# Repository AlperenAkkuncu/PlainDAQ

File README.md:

# PlainDAQ

PlainDAQ is a module that turns your Raspberry Pi Pico into a simple, precision 4-channel oscilloscope and a single channel function generator. Optionally it can also include a Wi-Fi module to add wireless capability to Raspberry Pi Pico modules.

To put it other words, PlainDAQ is a simple, useful tool to add basic precision analog functionality to your Raspberry Pi Pico board. It has a precision, low-noise, low-drift 12-bit 500kSPS/s ADC, sampling 4-channels and supporting 3 ranges (±1V, ±2V, ±4V). It also has a 10-bit DAC which helps create analog outputs and waveforms and it has a single range of ±4V.

Short List of features:

Analog Inputs:
• 4 Channels (multiplexed)  
• 12-bit resolution, 72dB SNR (11.6 ENOB,4000:1 dynamic range)  
• 500 kS/s sampling rate. 
• ±1V, ±2V, ±4V bipolar ranges.  

Analog Output:  
• 10-bit resolution.  
• 50 kS/s sampling rate.  
• ±4V bipolar range.  

Voltage Reference:
• 2.5V, 20ppm/°C (Typical) Drift  
• Calibrate to 0.05%, Stored in as ROM as calibration data. 

Bipolar Voltage Supply: 
• ±5V power output.   
• ±100mA current rating.    

ESP-WROOM-02D AT-Command Module:
• Simple UART interface to Raspberry Pico
• Wi-Fi connectivity    
• Shipped with ESP AT firmware 

# Here are some nice pictures of PlainDAQ

### Filter! More on that later

### The kit!

## PlainDAQ Connections

## PlainDAQ Components

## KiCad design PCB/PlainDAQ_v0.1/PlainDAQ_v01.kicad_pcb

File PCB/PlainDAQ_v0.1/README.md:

### !!DO NOT USE IT AS A REFERENCE!!
### This is an old version of PlainDAQ

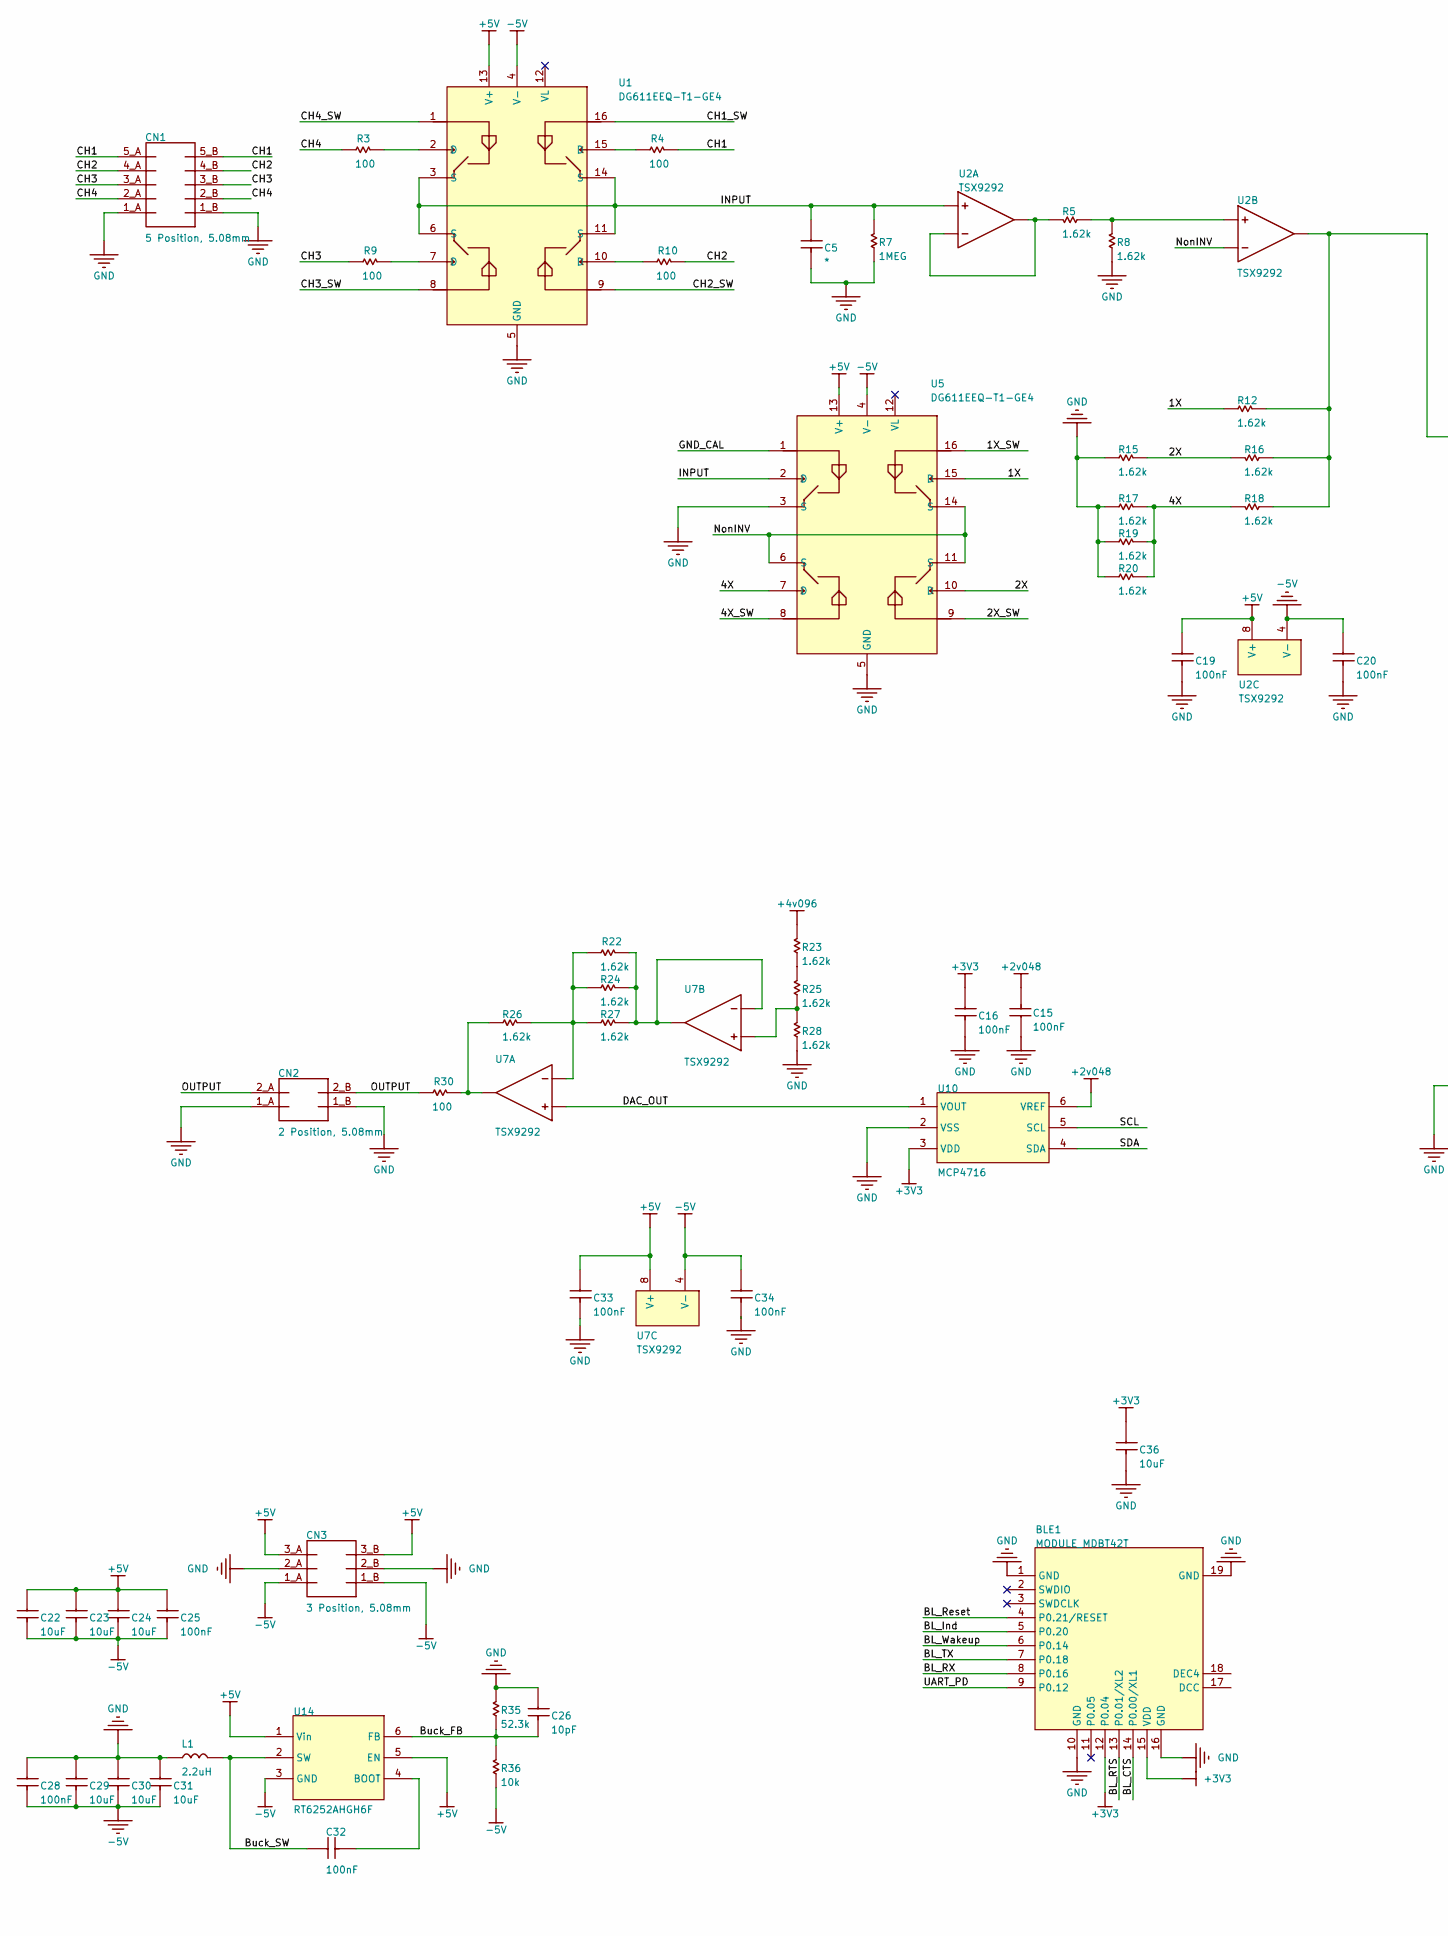
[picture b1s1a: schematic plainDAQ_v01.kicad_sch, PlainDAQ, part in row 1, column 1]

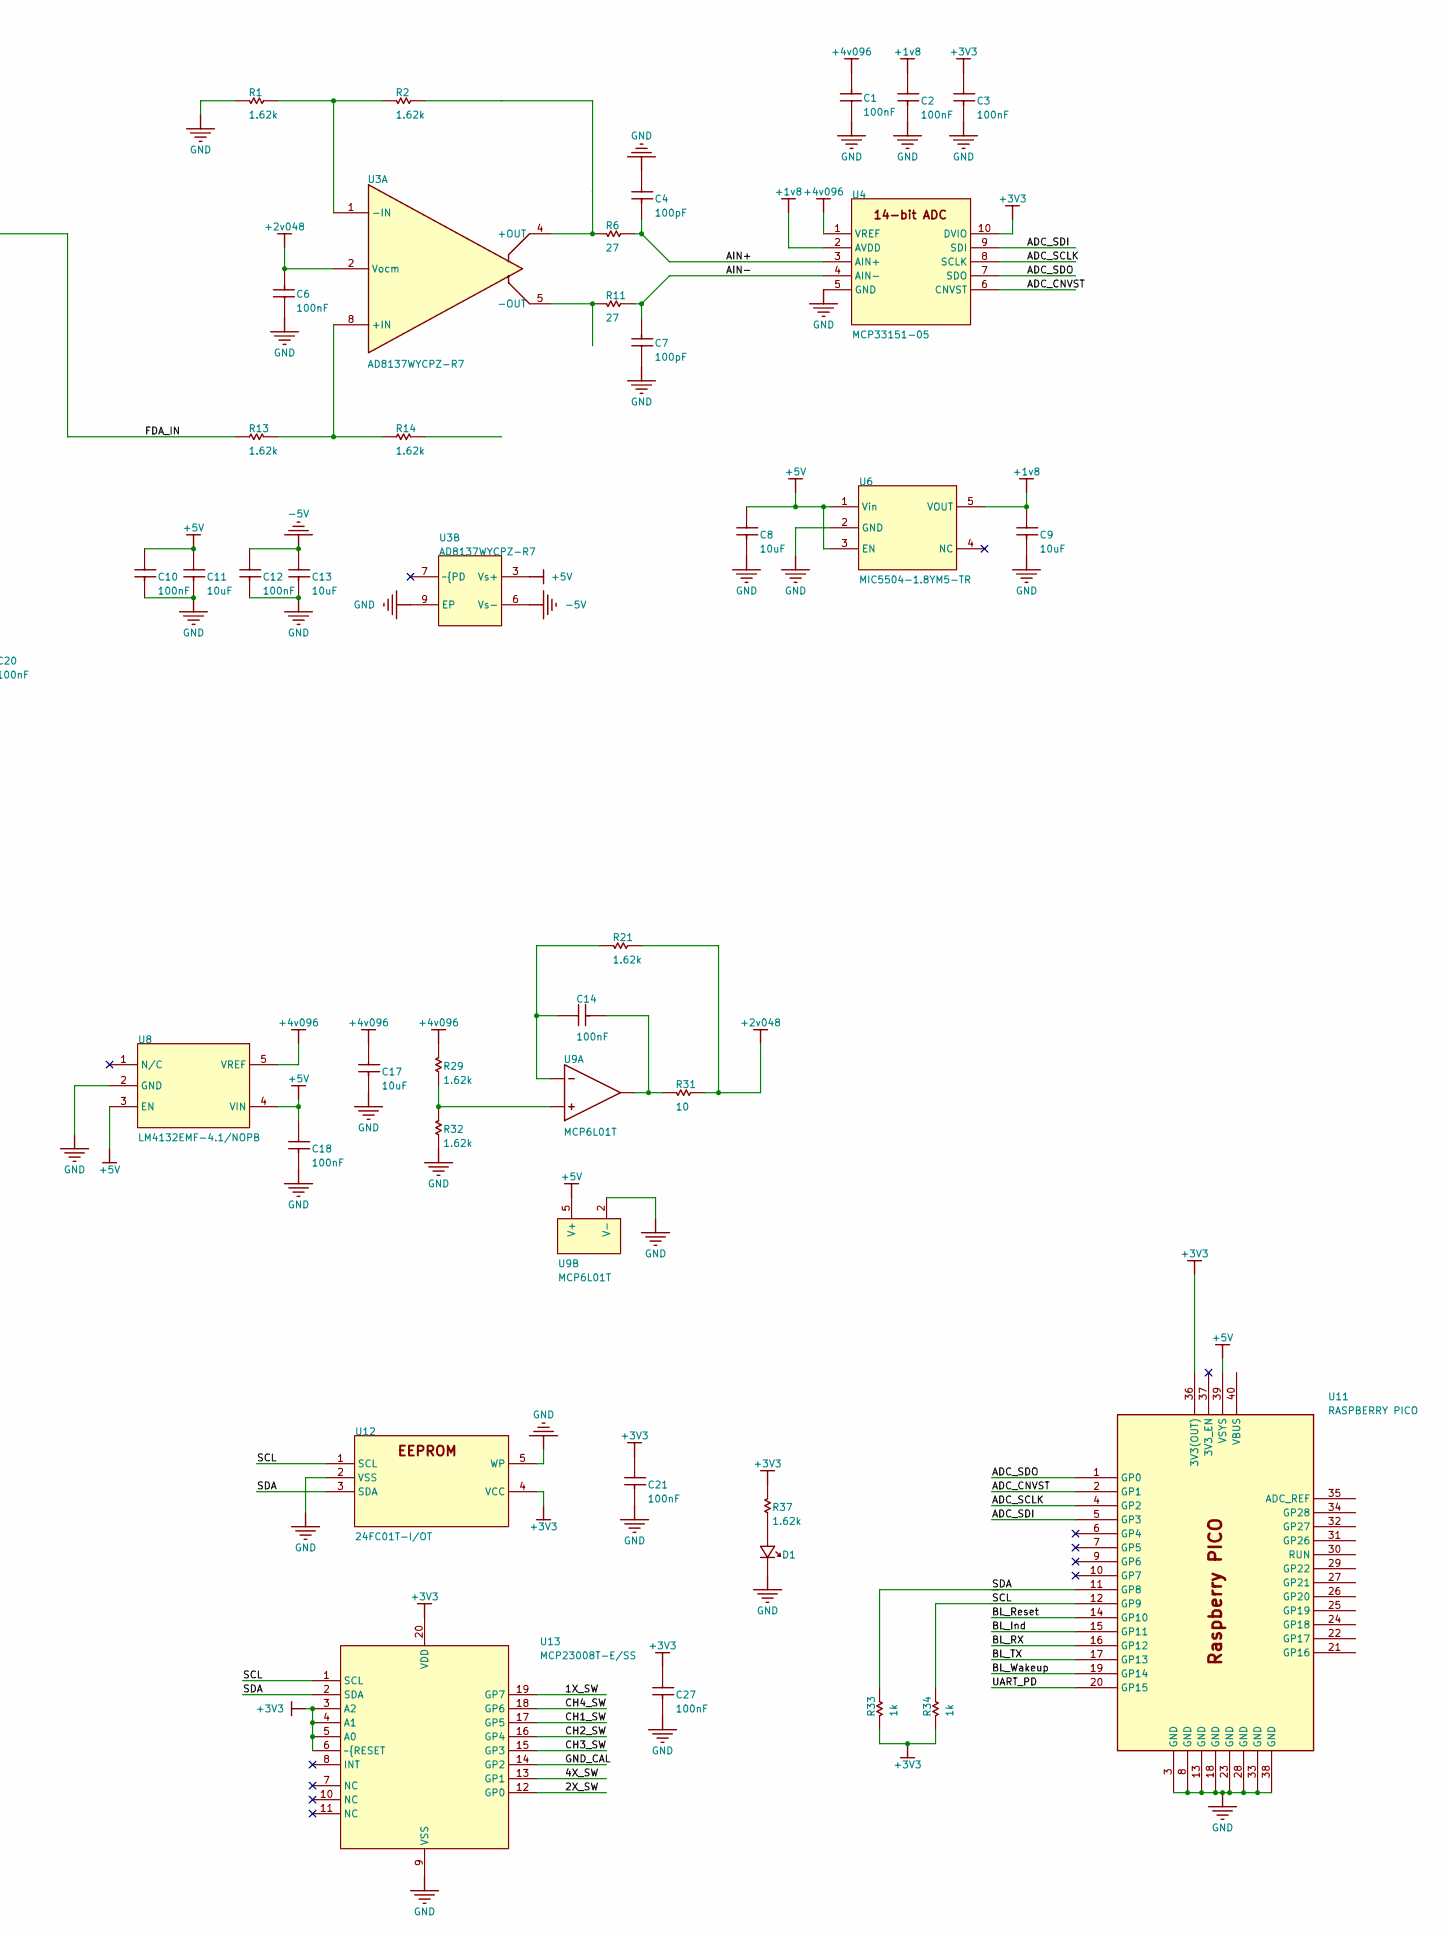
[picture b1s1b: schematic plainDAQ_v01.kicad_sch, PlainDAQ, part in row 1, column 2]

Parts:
BLE1: MODULE_MDBT42T; PCB_MDBT42T_7.2X11.2
C1, C2, C3, C6, C10, C12, C14, C15, C16, C18, C19, C20, C21, C25, C27, C28, C32, C33, C34: 100nF; CAP-0603; TOLERANCE *
C4, C7: 100pF; CAP-0603; TOLERANCE *
C5: *; CAP-0603; TOLERANCE 10pF
C8, C9, C11, C13, C17, C22, C23, C24, C29, C30, C31, C36: 10uF; CAP-0805; TOLERANCE *
C26: 10pF; CAP-0603; TOLERANCE *
CN1: 5 Position, 5.08mm; CUI_TBL004-508-05BE-2GY; MANUFACTURER P/N TBL004V-508-05BE-2GY
CN2: 2 Position, 5.08mm; CUI_TBL004-508-02BE-2GY; MANUFACTURER P/N TBL004V-508-02BE-2GY
CN3: 3 Position, 5.08mm; CUI_TBL004-508-03BE-2GY; MANUFACTURER P/N TBL004V-508-03BE-2GY
D1: 150060SS75000; LED-0603
L1: 2.2uH; IND-0806
R1, R2, R5, R8, R12, R13, R14, R15, R16, R17, R18, R19, R20, R21, R22, R23, R24, R25, R26, R27, R28, R29, R32, R37: 1.62k; Res-0603; TOLERANCE *
R3, R4, R9, R10, R30: 100; Res-0603; TOLERANCE *
R6, R11: 27; Res-0603; TOLERANCE *
R7: 1MEG; Res-0603; TOLERANCE *
R31: 10; Res-0603; TOLERANCE *
R33, R34: 1k; Res-0603; TOLERANCE *
R35: 52.3k; Res-0603; TOLERANCE *
R36: 10k; Res-0603; TOLERANCE *
U1, U5: DG611EEQ-T1-GE4; TSOP65P640X110-16N
U2, U7: TSX9292; TSOP6-8 4x4 (NO PAD); MANUFACTURER P/N TSX9292IST
U3: AD8137WYCPZ-R7; SON-8 3.0X3.0, 2.00x1.49 PAD
U4: MCP33151-05; TSSOP50P490X110-10N; MANUFACTURER P/N MCP33151-05-E/MS
U6: MIC5504-1.8YM5-TR; SOT95P280X100-5N
U8: LM4132EMF-4.1/NOPB; SOT95P280X100-5N
U9: MCP6L01T; SOT65P210X110-5N; MANUFACTURER P/N MCP6L01T-E/LT
U10: MCP4716; SOT95P275X110-6N; MANUFACTURER P/N MCP4716A2T-E/CH
U11: RASPBERRY PICO; Raspberry_PICO
U12: 24FC01T-I/OT; SOT65P210X110-5N
U13: MCP23008T-E/SS; SOP65P780X200-20N
U14: RT6252AHGH6F; SOTFL50P160X60-6N

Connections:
1X: R12.2, U5.15 (D)
1X_SW: U5.16, U13.19 (GP7)
2X: R15.1, R16.1, U5.10 (D)
2X_SW: U5.9, U13.12 (GP0)
4X: R17.1, R18.1, R19.1, R20.1, U5.7 (D)
4X_SW: U5.8, U13.13 (GP1)
+1v8: C2.2, C9.2, U4.2 (AVDD), U6.5 (VOUT)
+2v048: C6.1, C15.1, R21.2, R31.2, U3.2 (Vocm), U10.6 (VREF)
+3V3: BLE1.12 (P0.04), BLE1.15 (VDD), C3.2, C16.2, C21.2, C27.2, C36.2, R33.2, R34.2, R37.1, U4.10 (DVIO), U10.3 (VDD), U11.36 (3V3(OUT)), U12.4 (VCC), U13.3 (A2), U13.4 (A1), U13.5 (A0), U13.6 (~{RESET), U13.20 (VDD); also elsewhere on the board
+4v096: C1.1, C17.2, R23.1, R29.1, U4.1 (VREF), U8.5 (VREF)
+5V: C8.2, C10.2, C11.2, C18.2, C19.2, C22.2, C23.2, C24.2, C25.2, C33.2, CN3.3_A, CN3.3_B, U1.13 (V+), U2.8 (V+), U3.3 (Vs+), U5.13 (V+), U6.1 (Vin), U6.3 (EN), U7.8 (V+), U8.3 (EN), U8.4 (VIN), U9.5 (V+), U11.39 (VSYS), U14.1 (Vin), U14.5 (EN)
-5V: C12.2, C13.2, C20.2, C22.1, C23.1, C24.1, C25.1, C28.1, C29.1, C30.1, C31.1, C34.2, CN3.1_A, CN3.1_B, R36.1, U1.4 (V-), U2.4 (V-), U3.6 (Vs-), U5.4 (V-), U7.4 (V-), U14.3 (GND)
ADC_CNVST: U4.6 (CNVST), U11.2 (GP1)
ADC_SCLK: U4.8 (SCLK), U11.4 (GP2)
ADC_SDI: U4.9 (SDI), U11.5 (GP3)
ADC_SDO: U4.7 (SDO), U11.1 (GP0)
AIN+: C4.1, R6.1, U4.3 (AIN+)
AIN-: C7.1, R11.1, U4.4 (AIN-)
BL_Ind: BLE1.5 (P0.20), U11.15 (GP11); also elsewhere on the board
BL_RX: BLE1.8 (P0.16), U11.16 (GP12); also elsewhere on the board
BL_Reset: BLE1.4 (P0.21/RESET), U11.14 (GP10); also elsewhere on the board
BL_TX: BLE1.7 (P0.18), U11.17 (GP13); also elsewhere on the board
BL_Wakeup: BLE1.6 (P0.14), U11.19 (GP14); also elsewhere on the board
Buck_FB: C26.1, R35.1, R36.2, U14.6 (FB)
Buck_SW: C32.2, L1.2, U14.2 (SW)
CH1: CN1.5_A, CN1.5_B, R4.1
CH1_SW: U1.16, U13.17 (GP5)
CH2: CN1.4_A, CN1.4_B, R10.1
CH2_SW: U1.9, U13.16 (GP4)
CH3: CN1.3_A, CN1.3_B, R9.2
CH3_SW: U1.8, U13.15 (GP3)
CH4: CN1.2_A (3), CN1.2_B, R3.2
CH4_SW: U1.1, U13.18 (GP6)
DAC_OUT: U7.3 (+INA), U10.1 (VOUT)
FDA_IN: R12.1, R13.2, R16.2, R18.2, U2.7 (OUTB)
GND: BLE1.1 (GND), BLE1.10 (GND), BLE1.16 (GND), BLE1.19 (GND), C1.2, C2.1, C3.1, C4.2, C5.1, C6.2, C7.2, C8.1, C9.1, C10.1, C11.1, C12.1, C13.1, C15.2, C16.1, C17.1, C18.1, C19.1, C20.1, C21.1, C26.2, C27.1, C28.2, C29.2, C30.2, C31.2, C33.1, C34.1, C36.1, CN1.1_A, CN1.1_B, CN2.1_A, CN2.1_B, CN3.2_A (3), CN3.2_B, D1.1, L1.1, R1.2, R7.2, R8.2, R15.2, R17.2, R19.2, R20.2, R28.2, R32.2, R35.2, U1.5 (GND), U3.9 (EP), U4.5 (GND), U5.3 (S), U5.5 (GND), U6.2 (GND), U8.2 (GND), U9.2 (V-), U10.2 (VSS), U11.3 (GND), U11.8 (GND), U11.13 (GND), U11.18 (GND), U11.23 (GND), U11.28 (GND), U11.33 (GND), U11.38 (GND), U12.2 (VSS), U12.5 (WP), U13.9 (VSS); also elsewhere on the board
GND_CAL: U5.1, U13.14 (GP2)
INPUT: C5.2, R7.1, U1.3 (S), U1.6 (S), U1.11 (S), U1.14 (S), U2.3 (+INA), U5.2 (D)
NetC14_1: C14.1, R31.1, U9.1 (OUT)
NetC14_2: C14.2, R21.1, U9.4 (-IN)
NetC32_1: C32.1, U14.4 (BOOT)
NetD1_2: D1.2, R37.2
NetR1_1: R1.1, R2.2, U3.1 (-IN)
NetR2_1: R2.1, R6.2, U3.4 (+OUT)
NetR3_1: R3.1, U1.2 (D)
NetR4_2: R4.2, U1.15 (D)
NetR5_1: R5.1, R8.1, U2.5 (+INB)
NetR5_2: R5.2, U2.1 (OUTA), U2.2 (-INA)
NetR9_1: R9.1, U1.7 (D)
NetR10_2: R10.2, U1.10 (D)
NetR13_1: R13.1, R14.2, U3.8 (+IN)
NetR22_1: R22.1, R24.1, R27.1, U7.6 (-INB), U7.7 (OUTB)
NetR22_2: R22.2, R24.2, R26.1, R27.2, U7.2 (-INA)
NetR23_2: R23.2, R25.1
NetR25_2: R25.2, R28.1, U7.5 (+INB)
NetR26_2: R26.2, R30.1, U7.1 (OUTA)
NetR29_2: R29.2, R32.1, U9.3 (+IN)
NonINV: U2.6 (-INB), U5.6 (S), U5.11 (S), U5.14 (S)
OUTPUT: CN2.2_A (3), CN2.2_B, R30.2
SCL: R34.1, U10.5 (SCL), U11.12 (GP9), U12.1 (SCL), U13.1 (SCL)
SDA: R33.1, U10.4 (SDA), U11.11 (GP8), U12.3 (SDA), U13.2 (SDA)
UART_PD: BLE1.9 (P0.12), U11.20 (GP15); also elsewhere on the board

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
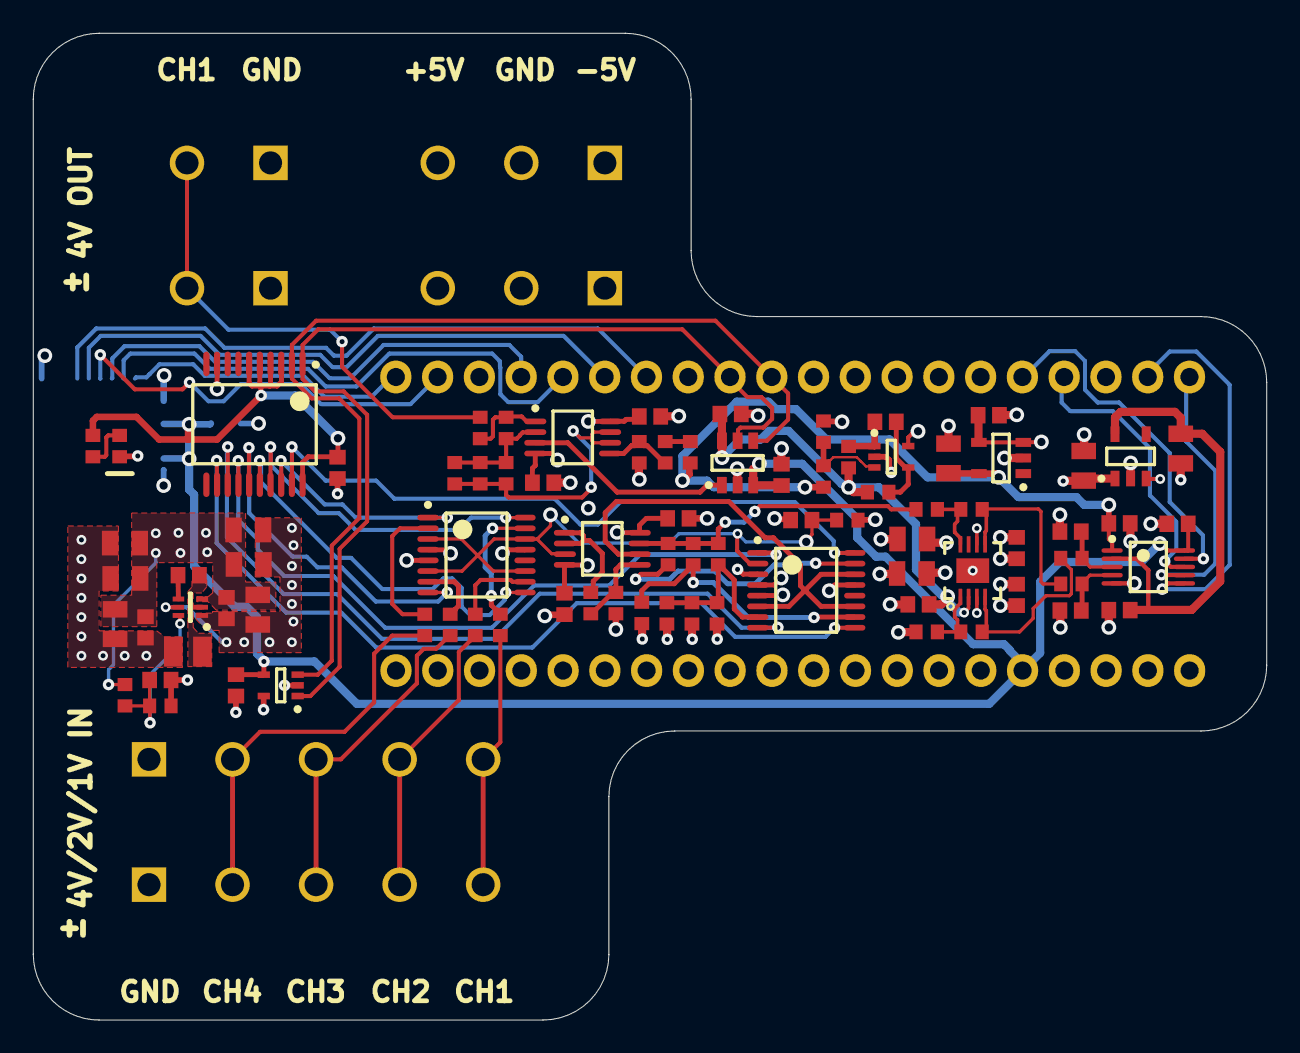
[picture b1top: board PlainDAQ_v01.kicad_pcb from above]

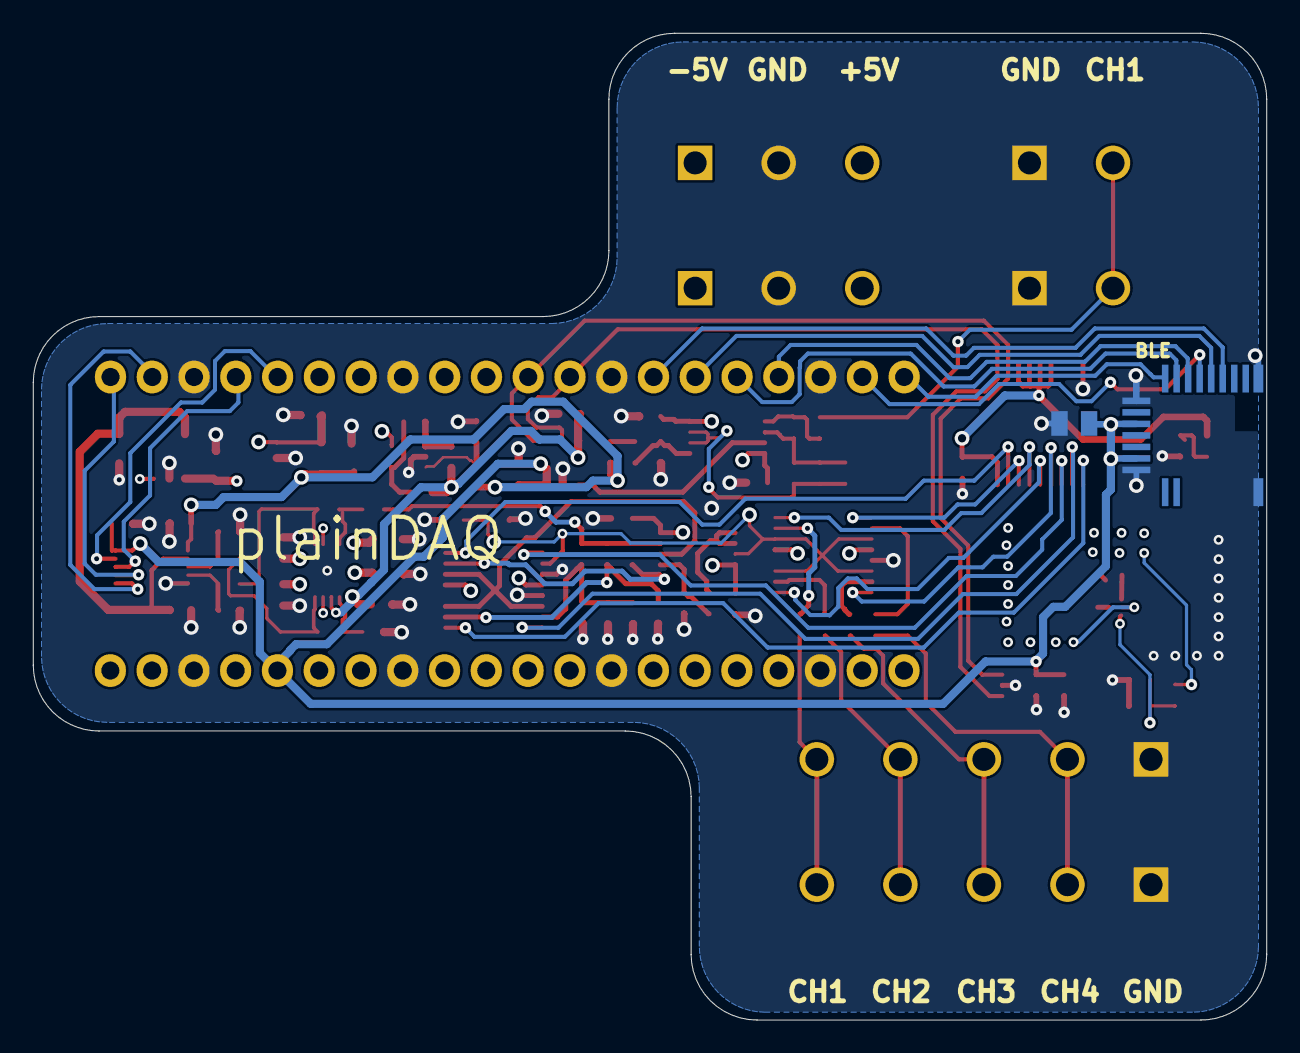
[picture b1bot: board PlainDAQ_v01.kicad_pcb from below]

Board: 4 copper layers, 75.0 x 60.0 mm, 90 parts (2 on the bottom side), 63 nets.

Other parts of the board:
BLE: MODULE_MDBT42T; PCB_MDBT42T_7.2X11.2

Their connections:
+3V3: BLE.12, BLE.15; also elsewhere on the board
BL_Ind: BLE.5; also elsewhere on the board
BL_RX: BLE.8; also elsewhere on the board
BL_Reset: BLE.4; also elsewhere on the board
BL_TX: BLE.7; also elsewhere on the board
BL_Wakeup: BLE.6; also elsewhere on the board
GND: BLE.1, BLE.10, BLE.16, BLE.19; also elsewhere on the board
UART_PD: BLE.9; also elsewhere on the board

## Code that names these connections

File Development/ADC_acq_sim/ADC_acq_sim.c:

/**
 * Copyright (c) 2020 Raspberry Pi (Trading) Ltd.
 *
 * SPDX-License-Identifier: BSD-3-Clause
 */

// Output PWM signals on pins 0 and 1

#define ADC_SDO 0
#define ADC_CNVST 1
#define ADC_SCLK 2
#define ADC_SDI 3
#define ADC_SDO_SIM 4

#define CLK_GEN_SM 0
#define GET_SAMPLE_SM 1
#define GEN_DATA_SM 2

#define IO_EXPANDER_ADDR 0x27
#define IODIR 0x00
#define IOPOL 0x01
#define OLAT 0x0A

#define CLK_FREQ 125000000
#define PWM_FREQ 500000

#include <stdio.h>
#include <math.h>
#include "pico/stdlib.h"
#include "hardware/pwm.h"
#include "hardware/clocks.h"
#include "hardware/pio.h"
#include "hardware/i2c.h"
#include "hardware/irq.h"
#include "ADC_acq_sim.pio.h"
#include "pico/binary_info.h"

uint16_t sample = 0;
uint32_t sample_tx_buff[4096], sample_rx_buff[4096];


void pio_sample_irq(){
    static uint32_t i = 0;
    irq_clear(PIO0_IRQ_0);
    if(i>4095){
        i = 0;
        sample_rx_buff[i] = pio_sm_get(pio0, GET_SAMPLE_SM);
        i++;
    }
    else{
        sample_rx_buff[i] = pio_sm_get(pio0, GET_SAMPLE_SM);
        i++;
    }
}

/*******************************************************************************
 * Function Declarations
 */
int reg_write(i2c_inst_t *i2c, 
                const uint addr, 
                const uint8_t reg, 
                uint8_t *buf,
                const uint8_t nbytes);

int reg_read(   i2c_inst_t *i2c,
                const uint addr,
                const uint8_t reg,
                uint8_t *buf,
                const uint8_t nbytes);

/*******************************************************************************
 * Function Definitions
 */

// Write 1 byte to the specified register
int reg_write(  i2c_inst_t *i2c, 
                const uint addr, 
                const uint8_t reg, 
                uint8_t *buf,
                const uint8_t nbytes) {

    int num_bytes_read = 0;
    uint8_t msg[nbytes + 1];

    // Check to make sure caller is sending 1 or more bytes
    if (nbytes < 1) {
        return 0;
    }

    // Append register address to front of data packet
    msg[0] = reg;
    for (int i = 0; i < nbytes; i++) {
        msg[i + 1] = buf[i];
    }

    // Write data to register(s) over I2C
    i2c_write_blocking(i2c, addr, msg, (nbytes + 1), false);

    return num_bytes_read;
}

// Read byte(s) from specified register. If nbytes > 1, read from consecutive
// registers.
int reg_read(  i2c_inst_t *i2c,
                const uint addr,
                const uint8_t reg,
                uint8_t *buf,
                const uint8_t nbytes) {

    int num_bytes_read = 0;

    // Check to make sure caller is asking for 1 or more bytes
    if (nbytes < 1) {
        return 0;
    }

    // Read data from register(s) over I2C
    i2c_write_blocking(i2c, addr, &reg, 1, true);
    num_bytes_read = i2c_read_blocking(i2c, addr, buf, nbytes, false);

    return num_bytes_read;
}

// I2C reserves some addresses for special purposes. We exclude these from the scan.
// These are any addresses of the form 000 0xxx or 111 1xxx
bool reserved_addr(uint8_t addr) {
    return (addr & 0x78) == 0 || (addr & 0x78) == 0x78;
}

void init_I2C(){
    i2c_init(i2c_default, 100 * 1000);
    gpio_set_function(8, GPIO_FUNC_I2C);
    gpio_set_function(9, GPIO_FUNC_I2C);
    gpio_pull_up(8);
    gpio_pull_up(9);
    // Make the I2C pins available to picotool
    bi_decl(bi_2pins_with_func(8, 9, GPIO_FUNC_I2C));
}

void set_channel_and_range(){
    uint8_t data;
    
    //setting channel one and range 1X
    //don't have much time to write a generic code...
    data = 0x5F;
    reg_write(i2c_default, IO_EXPANDER_ADDR, OLAT, &data,1);
    data = 0x00;
    reg_write(i2c_default, IO_EXPANDER_ADDR, IODIR, &data,1);
}

int main() {

       // Enable UART so we can print status output
    //stdio_init_all();

    /// \tag::ADC_SDI[]
    gpio_init(ADC_SDI);
    gpio_set_dir(ADC_SDI, GPIO_OUT);
    gpio_put(ADC_SDI, 1);
    /// \end::ADC_SDI[]
    
    /// \tag::i2c[]
    init_I2C();
    set_channel_and_range();
    /// \end::i2c[]

    /// \tag::pio[]
    // Choose PIO instance (0 or 1)
    PIO pio = pio0;
    PIO pio_1 = pio1;
    // Get first free state machine in PIO 0
    //uint sm_clk = pio_claim_unused_sm(pio, true);
    //uint sm_gen = pio_claim_unused_sm(pio_1, true);
    //uint sm_get_samples = pio_claim_unused_sm(pio, true);

    // Add PIO program to PIO instruction memory. SDK will find location and
    // return with the memory offset of the program.
    uint offset_clk = pio_add_program(pio0, &ADC_SCLK_gen_program);
    uint offset_gen = pio_add_program(pio0, &ADC_gen_sample_program);
    uint offset_get_sample = pio_add_program(pio0, &ADC_get_sample_program);

    // Initialize the program using the helper function in our .pio file
    ADC_SCLK_gen_init(pio0, CLK_GEN_SM, offset_clk, ADC_SCLK, 1);
    ADC_get_sample_init(pio0, GET_SAMPLE_SM, offset_get_sample,ADC_SDO_SIM);
    ADC_gen_sample_init(pio0, GEN_DATA_SM, offset_gen, ADC_SDO, 1);
    

    // Start running our PIO program in the state machine
    pio_sm_set_enabled(pio0, CLK_GEN_SM, true);
    pio_sm_set_enabled(pio0, GEN_DATA_SM, true);
    

    pio_set_irq0_source_enabled(pio0, pis_sm1_rx_fifo_not_empty, true);
    irq_set_exclusive_handler(PIO0_IRQ_0, &pio_sample_irq);
    irq_set_enabled(PIO0_IRQ_0, true);
    
    //pio0_hw->inte0 = PIO_IRQ0_INTE_SM0_BITS | PIO_IRQ0_INTE_SM1_BITS;
    /// \end::pio[]

    

    /// \tag::setup_pwm[]

    // Tell GPIO 0 and 1 they are allocated to the PWM
    //gpio_set_function(0, GPIO_FUNC_PWM);
    gpio_set_function(ADC_CNVST, GPIO_FUNC_PWM);

    // Find out which PWM slice is connected to GPIO 0 (it's slice 0)
    uint slice_num = pwm_gpio_to_slice_num(0);

    // Set period of 4 cycles (0 to 3 inclusive)
    pwm_set_wrap(slice_num, CLK_FREQ/PWM_FREQ );
    // Set initial B output high for three cycles before dropping
    // GPIO 1 is connected to PWM0B (datasheet page: 548)
    
    pwm_set_chan_level(slice_num, PWM_CHAN_B, 150);
    // Set the PWM running
    pwm_set_enabled(slice_num, true);
    /// \end::setup_pwm[]
    
    // Note we could also use pwm_set_gpio_level(gpio, x) which looks up the
    // correct slice and channel for a given GPIO.
    

    uint16_t i = sizeof(sample_tx_buff);
    
    for(i=0; i<( sizeof(sample_tx_buff)/4 ); i++){
        sample_tx_buff[i] = i;
        sample_rx_buff[i] = 0;
    }
        
    i = 0;

    pio_sm_set_enabled(pio0, GET_SAMPLE_SM, true);
    while(true){
                
        pio_sm_put_blocking(pio0, GEN_DATA_SM, (sample_tx_buff[i]<<20) );
        

        if( i >= (sizeof(sample_tx_buff)/4 - 1) )
            i = 0;
        else
            i++;

    }

}

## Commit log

2022-01-24 Create schematic_pdf
2022-01-24 Create adsa
2022-03-19 sinewave_stress_test.py
    Before I start developing GUI for PlainDAQ, I wanted to see how far I can push it.
    In this stress test I tried to use matplotlib's animation functionality, and pushed it to its limit.
    The interval of the animation is set 1ms to make it update the display as fast as possible. In each frame a 2000 sample long sinewave with different frequency, amplitude and phase is generated for th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
    It can achieve about 60FPS in my computer which more than I need.
2022-03-19 Create sinewave_stress_test.py
    Before I start developing GUI for PlainDAQ, I wanted to see how far I can push it.
    In this stress test I tried to use matplotlib's animation functionality, and pushed it to its limit.
    The interval of the animation is set 1ms to make it update the display as fast as possible. In each frame a 2000 sample long sinewave with different frequency, amplitude and phase is generated for th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
    It can achieve about 60FPS in my computer which more than I need.
2022-04-22 Create ADC_acq_sim
2022-06-05 init
2022-06-05 Create DAC_reconstruction
    DAC reconstruction filter simulation and comparison
2022-06-05 test
2022-06-05 Create DAC_reconstruction.asc
    DAC reconstruction filter simulation and comparison
2022-08-24 Delete schematic_pdf directory
    Deleted because it's an outdated version of PlainDAQ
2023-04-03 Type fixes in plaindaq_GUI
